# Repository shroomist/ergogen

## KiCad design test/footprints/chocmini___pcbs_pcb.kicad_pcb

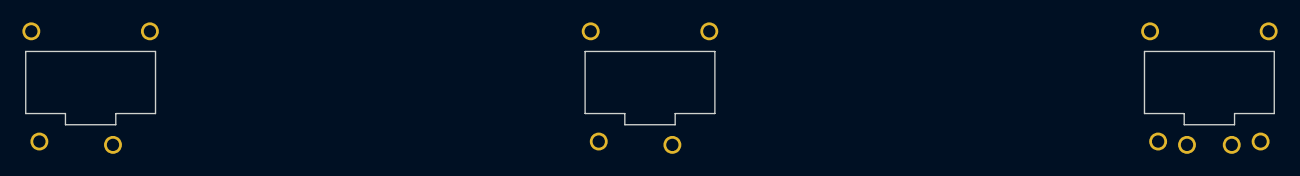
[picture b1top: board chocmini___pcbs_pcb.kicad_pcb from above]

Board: 2 copper layers, 3 parts (0 on the bottom side), 2 nets, no tracks yet.

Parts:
S1, S2, S3: Kailh_PG1232

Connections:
from: S1.1, S2.1, S3.1
to: S1.2, S2.2, S3.2

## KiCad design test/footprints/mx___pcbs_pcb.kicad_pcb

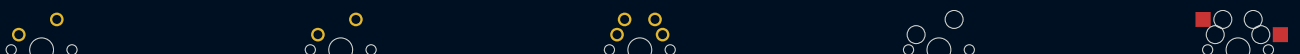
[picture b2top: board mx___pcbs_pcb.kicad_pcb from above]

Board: 2 copper layers, 5 parts (0 on the bottom side), 2 nets, no tracks yet.

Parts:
S1, S2, S3, S4, S5: MX

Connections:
from: S1.1, S2.1, S3.1, S4.1, S5.1
to: S1.2, S2.2, S3.2, S4.2, S5.2

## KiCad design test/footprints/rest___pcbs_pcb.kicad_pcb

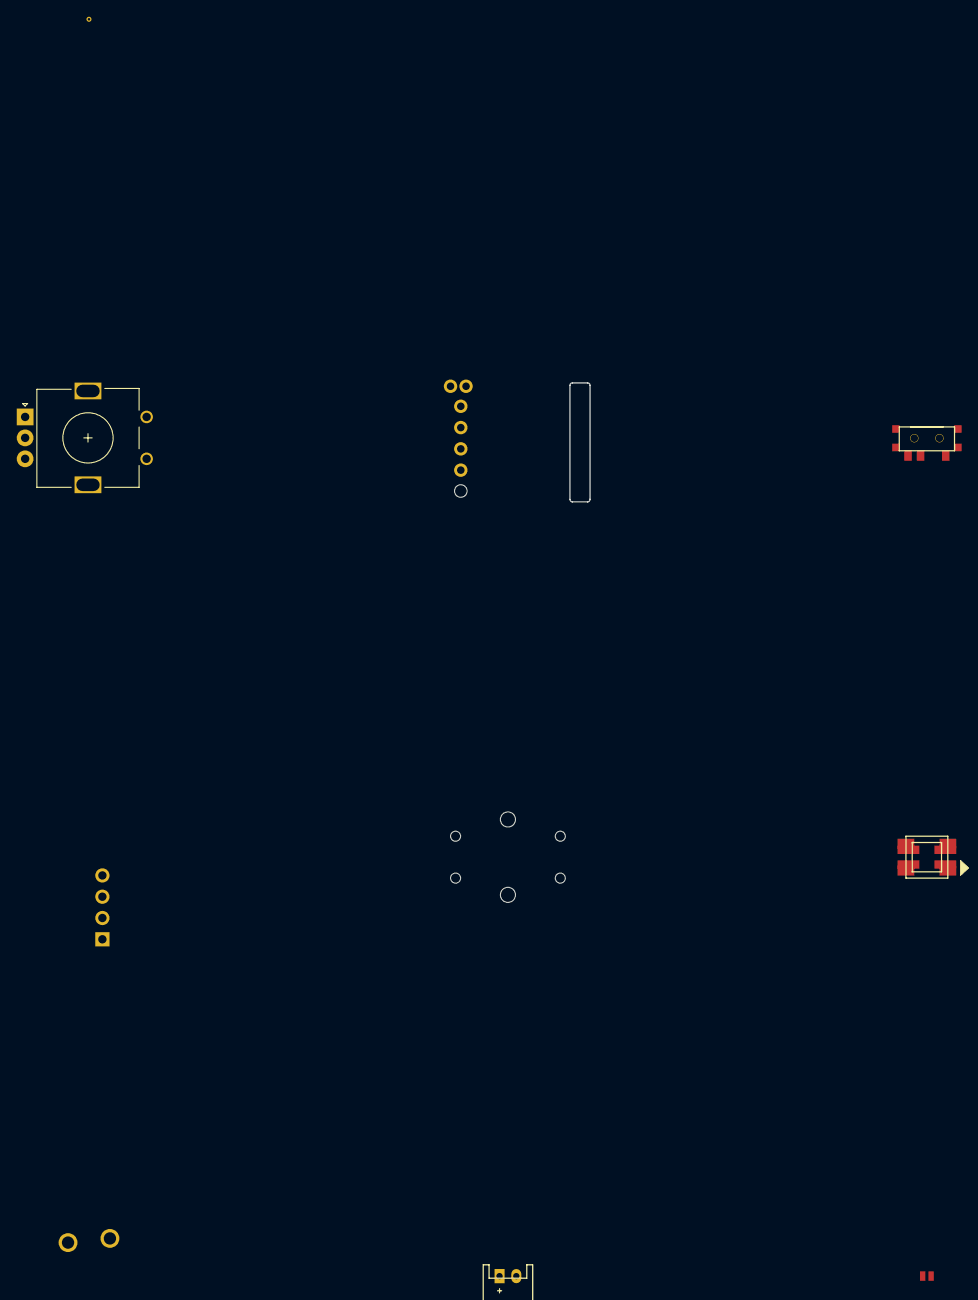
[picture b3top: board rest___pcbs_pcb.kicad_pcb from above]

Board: 2 copper layers, 9 parts (0 on the bottom side), 6 nets, no tracks yet.

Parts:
J1: Jumper; PCM12SMTR
JST1: JST_PH_S2B-PH-K_02x2.00mm_Angled
LED1: WS2812B
OLED1: OLED; OLED_headers
ROT1: rotary_encoder
S1: ALPS
S2: OMRON_B3F-4055
T1: SPDT_C128955
_1: VIA-0.6mm

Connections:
GND: LED1.3, LED1.33, OLED1.1
VCC: LED1.1, LED1.11, OLED1.2
din: LED1.4, LED1.44
dout: LED1.2, LED1.22
from: J1.1, ROT1.1, S1.1, S2.1, S2.2, T1.1
to: J1.2, ROT1.2, S1.2, S2.3, S2.4, T1.2

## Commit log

2023-01-13 Update footprints
2023-01-13 Add array type to footprints
2023-01-14 Update pcb to new Kicad format
2023-01-14 Update tentingpuck to new Kicad format
2023-01-14 Update scrollwheel to new Kicad format
2023-01-18 FEAT: Add a separate netclass with wider traces for power
2023-01-18 TEST: Fix tests for new power netclass
2023-01-18 Add simple via.
    Add new simple via footprint, aligned with https://dev-docs.kicad.org/en/file-formats/sexpr-pcb/#_track_via_syntax
2023-01-21 Add logo and side indicator to BOM exclusion
2023-01-21 ...and from position files
2023-01-24 Add diode symbol to silkscreen
2023-01-24 Add proper side to Jumper
2023-01-25 Add new porcupine logo
